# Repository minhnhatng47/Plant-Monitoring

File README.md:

# Plant-Monitoring-CPS

## Giới thiệu

**Plant-Monitoring-CPS** là mô hình hệ thống Cyber-Physical System (CPS) ứng dụng trong giám sát và chăm sóc cây trồng. Hệ thống tích hợp các công nghệ IoT, MQTT, Edge AI, cơ sở dữ liệu thời gian thực và mô hình Digital Twin trên Unity nhằm thu thập dữ liệu môi trường, xử lý tại biên, điều khiển thiết bị và trực quan hóa trạng thái cây trồng theo thời gian thực.

Đề tài được xây dựng cho mô hình chăm sóc rau cải mầm (*Brassica juncea*) trong môi trường thử nghiệm. Hệ thống có khả năng đo các thông số như nhiệt độ, độ ẩm không khí, độ ẩm đất và cường độ ánh sáng. Dữ liệu được gửi từ ESP32 về Raspberry Pi thông qua MQTT, sau đó được xử lý, lưu trữ, hiển thị trên Web Dashboard và đồng bộ với mô hình Digital Twin trong Unity.

## Mục tiêu dự án

Dự án hướng đến việc xây dựng một mô hình CPS hoàn chỉnh cho chăm sóc cây trồng thông minh với các mục tiêu chính:

- Thu thập dữ liệu môi trường từ các cảm biến.
- Truyền dữ liệu giữa ESP32, Raspberry Pi, Web Dashboard và Unity thông qua MQTT.
- Lưu trữ dữ liệu cảm biến theo thời gian thực bằng InfluxDB.
- Xử lý dữ liệu tại biên bằng Raspberry Pi.
- Ứng dụng mô hình Machine Learning để hỗ trợ quyết định bật/tắt bơm tưới.
- Điều khiển thiết bị chấp hành như relay, máy bơm và đèn.
- Xây dựng mô hình Digital Twin 3D trên Unity để mô phỏng trạng thái hệ thống.
- Hỗ trợ điều khiển hai chiều từ Web Dashboard và Unity xuống phần cứng thực tế.

## Kiến trúc hệ thống

Luồng hoạt động tổng quát của hệ thống:

```text
Cảm biến môi trường
        ↓
      ESP32
        ↓ MQTT
Raspberry Pi / MQTT Broker
        ↓
Edge Processing + AI Model
        ↓
InfluxDB + FastAPI Backend
        ↓
Web Dashboard / Unity Digital Twin
        ↓
Lệnh điều khiển thiết bị
        ↓
ESP32 → Relay → Bơm / Đèn
```

Trong đó:

- **ESP32** đọc dữ liệu cảm biến và điều khiển thiết bị chấp hành.
- **MQTT Broker Mosquitto** làm trung gian truyền nhận dữ liệu.
- **Raspberry Pi 4B** đóng vai trò Edge Gateway để xử lý dữ liệu, chạy AI và lưu trữ.
- **InfluxDB** lưu dữ liệu cảm biến dạng chuỗi thời gian.
- **FastAPI Backend** cung cấp API và WebSocket cho giao diện.
- **Web Dashboard** hiển thị dữ liệu và điều khiển thiết bị.
- **Unity Digital Twin** mô phỏng nhà kính, cây trồng và trạng thái thiết bị trong môi trường 3D.

## Chức năng chính

### 1. Giám sát dữ liệu môi trường

Hệ thống thu thập các thông số chính:

- Nhiệt độ không khí
- Độ ẩm không khí
- Độ ẩm đất
- Cường độ ánh sáng
- Trạng thái bơm
- Trạng thái đèn
- Trạng thái hệ thống

### 2. Truyền nhận dữ liệu MQTT

ESP32 publish dữ liệu cảm biến lên MQTT Broker. Raspberry Pi, Web Dashboard và Unity có thể subscribe các topic tương ứng để nhận dữ liệu realtime.

MQTT được sử dụng để:

- Gửi dữ liệu cảm biến từ ESP32 lên Raspberry Pi.
- Gửi lệnh điều khiển từ Raspberry Pi/Web/Unity xuống ESP32.
- Đồng bộ trạng thái thiết bị giữa phần cứng và giao diện.
- Kiểm tra khả năng truyền nhận dữ liệu hai chiều.

### 3. Edge AI trên Raspberry Pi

Raspberry Pi xử lý dữ liệu tại biên và chạy mô hình Machine Learning để hỗ trợ quyết định tưới nước. Mô hình AI sử dụng dữ liệu cảm biến để dự đoán trạng thái cần tưới hoặc không cần tưới.

Quy trình AI:

```text
Dữ liệu cảm biến → Tiền xử lý → Random Forest Model → Dự đoán trạng thái bơm → Gửi lệnh điều khiển
```

Mô hình chính được sử dụng:

- Random Forest

Các tiêu chí đánh giá:

- Accuracy
- Precision
- Recall
- F1-score
- Confusion Matrix
- Feature Importance

### 4. Điều khiển thiết bị

Hệ thống có thể điều khiển:

- Máy bơm nước
- Đèn chiếu sáng
- Relay
- Chức năng START hệ thống

Thiết bị có thể được điều khiển từ:

- Web Dashboard
- Unity Digital Twin
- Logic tự động từ AI
- Lệnh MQTT

### 5. Web Dashboard

Web Dashboard dùng để:

- Hiển thị dữ liệu cảm biến realtime.
- Theo dõi trạng thái bơm và đèn.
- Gửi lệnh điều khiển thiết bị.
- Quan sát lịch sử dữ liệu.
- Kiểm tra trạng thái hoạt động của hệ thống.

### 6. Unity Digital Twin

Unity Digital Twin mô phỏng hệ thống chăm sóc cây trồng trong môi trường 3D.

Các chức năng chính:

- Hiển thị mô hình nhà kính.
- Hiển thị dữ liệu cảm biến realtime.
- Hiển thị trạng thái bơm, đèn và cây trồng.
- Mô phỏng các giai đoạn phát triển của cây.
- Điều khiển thiết bị từ giao diện Unity.
- Đồng bộ trạng thái giữa mô hình số và hệ thống vật lý.

## Phần cứng sử dụng

| Thiết bị | Vai trò |
|---|---|
| ESP32 | Đọc cảm biến, gửi dữ liệu MQTT, điều khiển relay |
| Raspberry Pi 4B | Gateway xử lý biên, MQTT Broker, AI, lưu trữ dữ liệu |
| DHT11 | Đo nhiệt độ và độ ẩm không khí |
| Cảm biến độ ẩm đất | Đo độ ẩm đất |
| BH1750 | Đo cường độ ánh sáng |
| ADS1115 | Chuyển đổi tín hiệu analog sang digital |
| DS3231 | Cung cấp thời gian thực |
| Relay | Đóng/ngắt thiết bị chấp hành |
| Máy bơm mini | Tưới nước tự động |
| Đèn chiếu sáng | Bổ sung ánh sáng cho cây |
| Nguồn DC | Cấp nguồn cho hệ thống |

## Công nghệ sử dụng

| Thành phần | Công nghệ |
|---|---|
| Vi điều khiển | ESP32 |
| Gateway | Raspberry Pi 4B |
| Giao thức truyền thông | MQTT |
| MQTT Broker | Mosquitto |
| Backend | FastAPI |
| Database | InfluxDB |
| AI / Machine Learning | Python, Random Forest |
| Dashboard | Web Dashboard |
| Digital Twin | Unity |
| Dữ liệu huấn luyện | CSV |
| Ngôn ngữ lập trình | C/C++, Python, C#, JavaScript |

## Cấu trúc thư mục

```text
Plant-Monitoring/
│
├── BBB/
│   └── Xử lý biên, gateway hoặc các file liên quan đến Raspberry Pi
│
├── Hardware/
│   └── node_sensor/
│       └── Mã nguồn và thiết kế phần cảm biến
│
├── Web/
│   └── Giao diện Web Dashboard
│
├── esp32/
│   └── Firmware ESP32 đọc cảm biến và điều khiển thiết bị
│
├── Plant_DigitalTwin/
│   ├── Assets/
│   ├── Packages/
│   ├── ProjectSettings/
│   ├── file_csv/
│   ├── analyze_growth_from_old_csv.py
│   ├── analyze_plant_growth.py
│   └── generate_sample_csv.py
│
├── README.md
└── .gitignore
```

## Luồng dữ liệu hệ thống

1. ESP32 đọc dữ liệu từ cảm biến.
2. ESP32 đóng gói dữ liệu thành JSON.
3. ESP32 publish dữ liệu lên MQTT Broker.
4. Raspberry Pi subscribe dữ liệu từ MQTT Broker.
5. Raspberry Pi xử lý dữ liệu và lưu vào InfluxDB.
6. Mô hình AI dự đoán trạng thái cần tưới hoặc không cần tưới.
7. Raspberry Pi gửi lệnh điều khiển xuống ESP32 qua MQTT.
8. ESP32 điều khiển relay để bật/tắt bơm hoặc đèn.
9. Web Dashboard và Unity Digital Twin cập nhật trạng thái realtime.
10. Người dùng có thể điều khiển ngược lại từ Web hoặc Unity.

## Cài đặt và chạy hệ thống

### 1. Clone repository

```bash
git clone https://github.com/minhnhatng47/Plant-Monitoring.git
cd Plant-Monitoring
```

### 2. Cài đặt MQTT Broker trên Raspberry Pi

```bash
sudo apt update
sudo apt install mosquitto mosquitto-clients
sudo systemctl enable mosquitto
sudo systemctl start mosquitto
```

Kiểm tra trạng thái Mosquitto:

```bash
sudo systemctl status mosquitto
```

### 3. Chạy Backend / Gateway

Di chuyển vào thư mục chứa chương trình xử lý trên Raspberry Pi, sau đó cài các thư viện cần thiết:

```bash
pip install -r requirements.txt
```

Chạy chương trình:

```bash
python main.py
```

Lưu ý: tên file chạy thực tế có thể thay đổi tùy theo cấu trúc code trong thư mục gateway/backend.

### 4. Nạp code ESP32

Mở thư mục `esp32/` bằng Arduino IDE hoặc PlatformIO.

Cấu hình các thông tin cần thiết trong code:

```cpp
WiFi SSID
WiFi Password
MQTT Broker IP
MQTT Port
MQTT Topics
```

Sau đó nạp chương trình vào ESP32.

### 5. Chạy Web Dashboard

Mở thư mục `Web/`.

Nếu là web tĩnh, có thể mở trực tiếp:

```text
index.html
```

Nếu có server riêng, chạy theo file hướng dẫn hoặc file cấu hình trong thư mục `Web`.

### 6. Mở Unity Digital Twin

Mở Unity Hub, chọn thư mục:

```text
Plant_DigitalTwin/
```

Sau đó mở project bằng Unity.

Các thư mục quan trọng cần giữ nguyên:

```text
Assets/
Packages/
ProjectSettings/
```

Không nên xóa các file `.meta` trong project Unity vì Unity cần các file này để nhận diện asset.

## Dữ liệu AI

Dữ liệu huấn luyện AI được lưu dưới dạng CSV trong thư mục:

```text
Plant_DigitalTwin/file_csv/
```

Các script Python dùng để phân tích dữ liệu sinh trưởng:

```text
analyze_growth_from_old_csv.py
analyze_plant_growth.py
generate_sample_csv.py
```

Dữ liệu được sử dụng để:

- Kiểm tra dữ liệu thiếu.
- Phân tích đặc trưng đầu vào.
- Thống kê trạng thái bơm.
- Huấn luyện mô hình Random Forest.
- Đánh giá mô hình AI.
- Mô phỏng tăng trưởng cây trong Unity.

## Kết quả đạt được

Dự án đã xây dựng được mô hình CPS chăm sóc cây trồng gồm đầy đủ các thành phần:

- Phần cứng cảm biến và thiết bị chấp hành.
- Truyền nhận dữ liệu hai chiều qua MQTT.
- Lưu trữ dữ liệu cảm biến bằng InfluxDB.
- Điều khiển thiết bị từ Web Dashboard.
- Điều khiển thiết bị từ Unity Digital Twin.
- Huấn luyện mô hình Random Forest để hỗ trợ quyết định tưới.
- Mô phỏng trạng thái cây trồng và thiết bị trên Unity.
- Hiển thị dữ liệu realtime và trạng thái sinh trưởng của cây.

## Hạn chế

Một số hạn chế hiện tại của hệ thống:

- Mô hình mới triển khai ở quy mô thử nghiệm.
- Cảm biến sử dụng có độ chính xác phù hợp cho mô hình học tập, chưa phải thiết bị công nghiệp.
- AI chủ yếu tập trung vào quyết định bật/tắt bơm, chưa mở rộng sang nhận diện bệnh cây hoặc tối ưu đa mục tiêu.
- Digital Twin chủ yếu mô phỏng trạng thái và tăng trưởng cơ bản, chưa mô phỏng đầy đủ các quá trình sinh học phức tạp.
- Hệ thống chưa triển khai bảo mật nâng cao cho MQTT, API và dashboard.

## Hướng phát triển

Trong tương lai, hệ thống có thể được mở rộng theo các hướng:

- Bổ sung thêm cảm biến pH, EC, CO2 hoặc camera.
- Nâng cấp mô hình AI để dự đoán sinh trưởng cây trồng.
- Ứng dụng Computer Vision để nhận diện bệnh cây.
- Triển khai MQTT bảo mật bằng username/password hoặc TLS.
- Xây dựng dashboard hoàn chỉnh hơn với phân quyền người dùng.
- Đồng bộ dữ liệu lên cloud để theo dõi từ xa.
- Tối ưu mô hình Digital Twin để mô phỏng chính xác hơn.
- Triển khai hệ thống trên mô hình nhà kính quy mô lớn hơn.

## Thành viên nhóm

| STT | Họ và tên | MSSV |
|---|---|---|
| 1 | Lê Lữ Nhật An | 23139001 |
| 2 | Nguyễn Trần Minh Đức | 23139012 |
| 3 | Nguyễn Minh Nhật | 23139032 |
| 4 | Trà Hồng Phượng | 23139035 |
| 5 | Lê Đức Trí | 23139049 |

## Thông tin môn học

- Môn học: Hệ thống CPS
- Đề tài: Thiết kế và thi công mô hình hệ thống CPS tích hợp IoT, AI và Unity
- Giảng viên hướng dẫn: ThS. Trịnh Quốc Thanh
- Trường: Đại học Công nghệ Kỹ thuật TP. Hồ Chí Minh
- Khoa: Điện - Điện tử

## License

Dự án được thực hiện phục vụ mục đích học tập, nghiên cứu và thực nghiệm trong môn học Hệ thống CPS.

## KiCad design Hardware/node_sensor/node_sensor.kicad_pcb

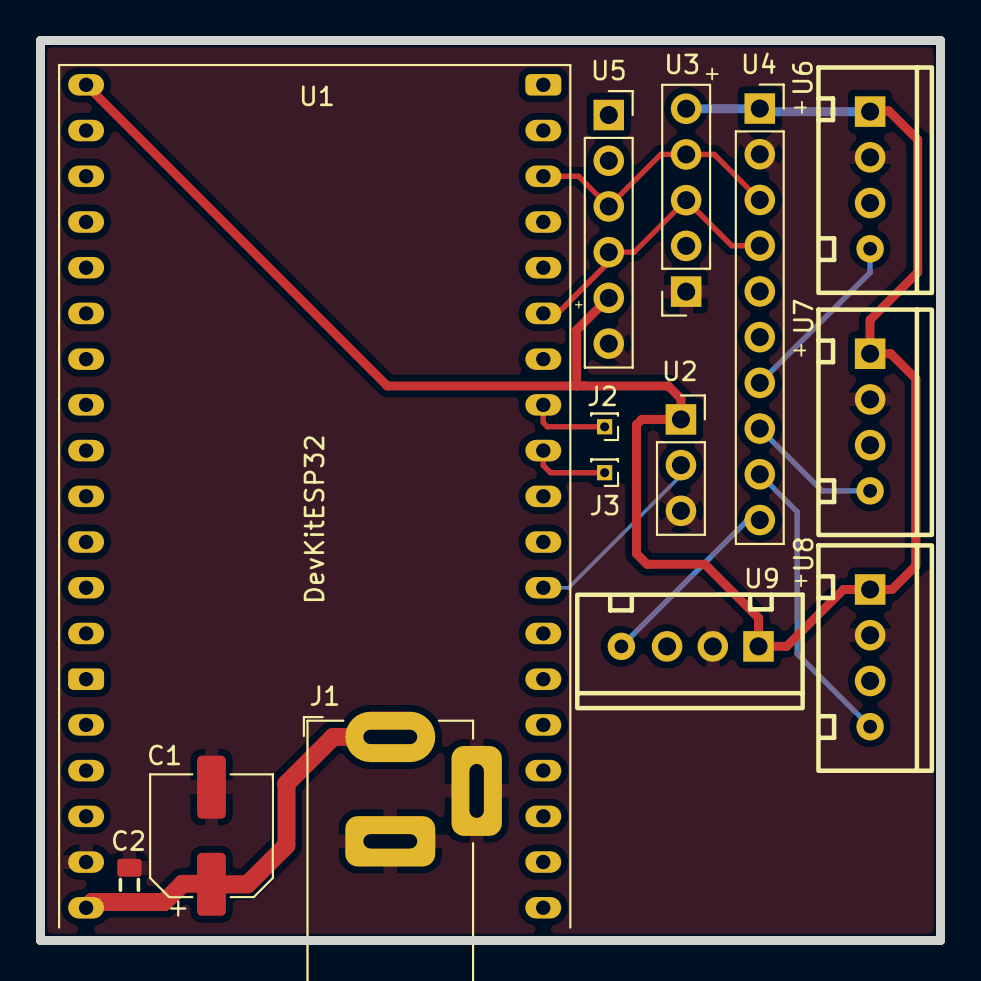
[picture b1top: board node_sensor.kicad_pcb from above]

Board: 2 copper layers, 50.0 x 50.0 mm, 14 parts (0 on the bottom side), 12 nets.

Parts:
C1: 470uF; CP_Elec_6.3x7.7
C2: 0.1uF; C_0805
J1: Conn_Jack-DC; BarrelJack_Horizontal
J2: Pump; PinHeader_1x01_P1.00mm_Vertical
J3: Light; PinHeader_1x01_P1.00mm_Vertical
U1: DevKitESP32; ESP32-DevKitC
U2: DHT11; PinSocket_1x03_P2.54mm_Vertical
U3: BH1750; PinSocket_1x05_P2.54mm_Vertical
U4: ADS1115; PinSocket_1x10_P2.54mm_Vertical
U5: DS3231; PinSocket_1x06_P2.54mm_Vertical
U6, U7, U8, U9: Soil-Moisture; Conn_XH-P2.54mm-4P

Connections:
+3V3: U1.1 (3V), U2.1 (VCC), U3.5 (VCC), U4.1 (VCC), U5.5 (VCC), U6.1 (VCC), U7.1 (VCC), U8.1 (VCC), U9.1 (VCC)
+5V: C1.1, C2.1, J1.1, U1.19 (5V)
/1_wire: U1.27 (16), U2.2 (D0)
/I2C_SCL: U1.36 (22), U3.4 (SCL), U4.3 (SCL), U5.3 (SCL)
/I2C_SDA: U1.33 (21), U3.3 (SDA), U4.4 (SDA), U5.4 (SDA)
GND: C1.2, C2.2, J1.2, J1.3, U1.18 (GND), U2.3 (GND), U3.1 (GND), U4.2 (GND), U5.6 (GND), U6.2 (GND), U7.2 (GND), U8.2 (GND), U9.2 (GND)
unnamed: J2.1 (Pin_1_1), U1.31 (19)
unnamed: J3.1 (Pin_1_1), U1.30 (18)
unnamed: U4.7 (A0), U6.4 (A0)
unnamed: U4.8 (A1), U7.4 (A0)
unnamed: U4.9 (A2), U8.4 (A0)
unnamed: U4.10 (A3), U9.4 (A0)

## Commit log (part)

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2026-05-18 upadted lib sensor
2026-05-18 updated driver + modified v6
2026-05-18 modified and tunned sensor
2026-05-20 created folder BBB
2026-05-21 updated gateway.py
2026-05-23 updated esp32 v2
2026-05-24 changed phase awaness flow
2026-05-24 modifed model_config.j
2026-05-24 updated hardware + fixed conflict Gatway
2026-05-25 modified model with phase
2026-05-26 "updated topic DT in Unity"
2026-05-26 updated flow DT
2026-05-27 updated nvs saved start timer
2026-05-28 modified topic and name Table
2026-05-29 updated script clear DB
2026-06-12 web v3
2026-06-13 modified web v3
2026-06-15 web/app
2026-06-16 add token
2026-06-27 turn off AI
